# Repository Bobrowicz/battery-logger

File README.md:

# battery-logger
Repository for my digitally controlled dummy load/battery tester

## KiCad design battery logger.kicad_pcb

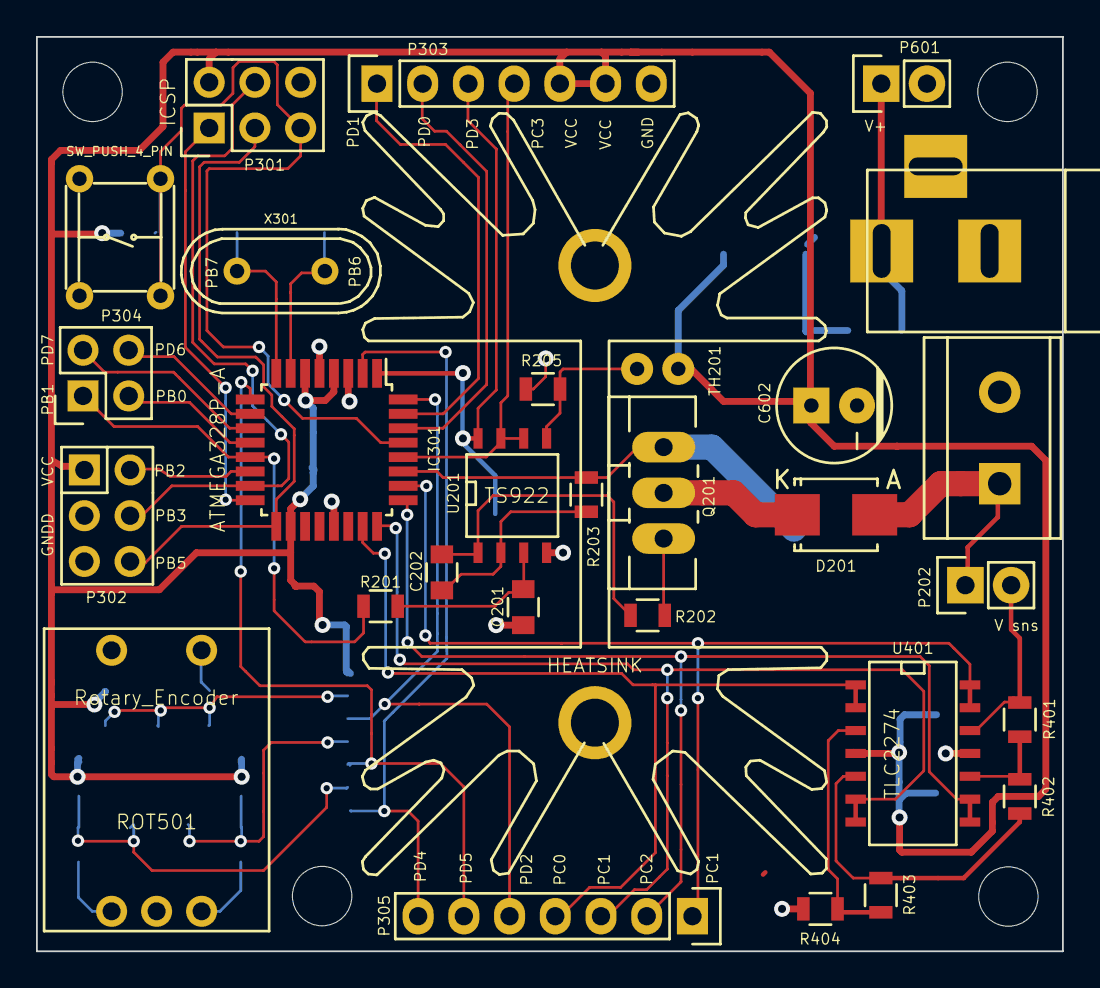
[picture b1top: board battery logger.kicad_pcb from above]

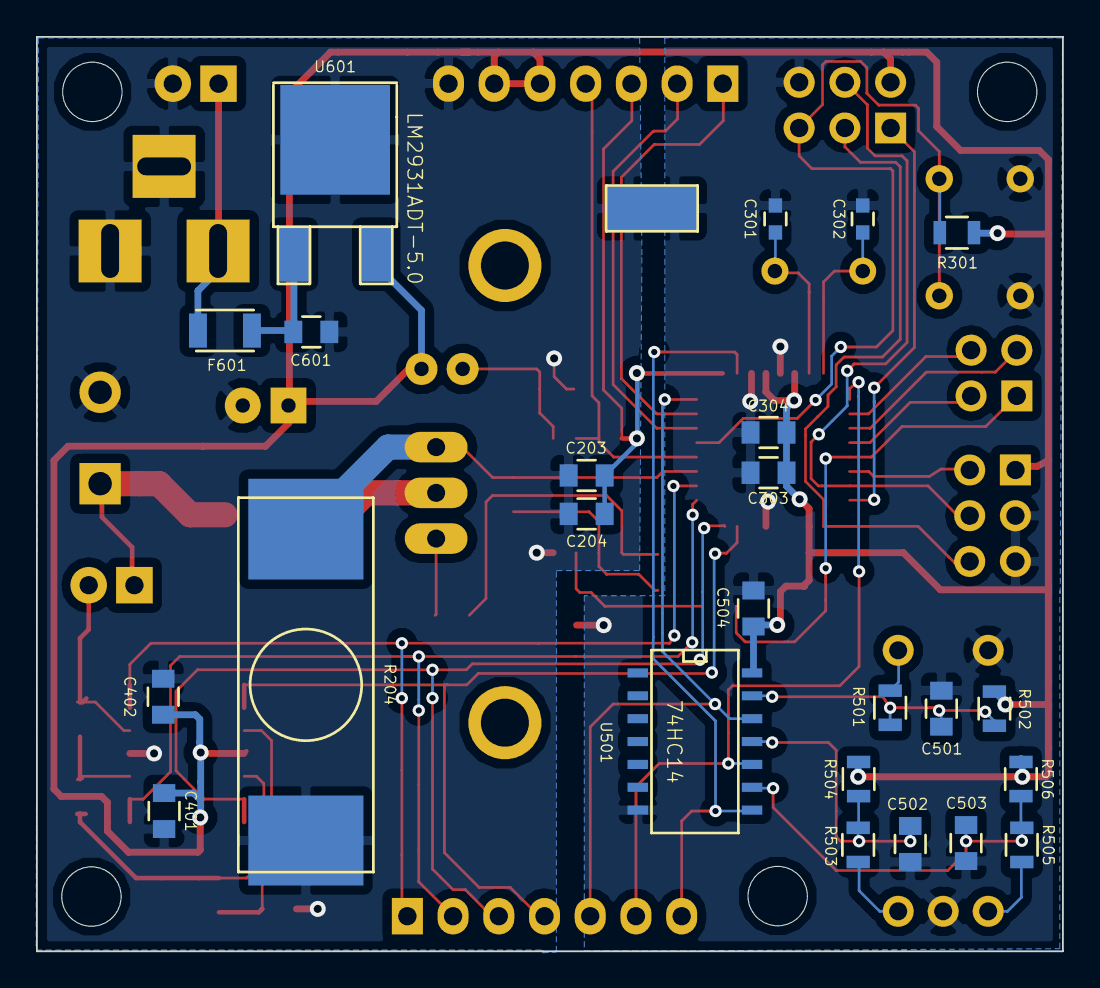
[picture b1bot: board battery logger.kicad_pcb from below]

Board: 2 copper layers, 57.0 x 50.8 mm, 59 parts (25 on the bottom side), 45 nets.

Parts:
C201, C202, C203, C402, C501: 1u; C_0805
C204, C303, C401, C504, C601: 0.1u; C_0805
C301, C302: 18p; C_0603
C304, C502, C503: 0.01u; C_0805
C602: 100u; Capacitor6.4x6RM2.5
CON601: BARREL_JACK
D201: DIODESCH; Diode-SMB_Standard
F601: FUSE; PTC_1206
HS201: HEATSINK; FA-TO220-64E
IC301: ATMEGA328P-A; TQFP-32_7x7mm_Pitch0.8mm
J601: Net_Tie; Net_Tie2
M3 screw hole, M3 screw hole#2, M3 screw hole#3, M3 screw hole#4: VAL**; M3_screw_hole
P201: CONN_01X02; Terminal_Block_1x2_5.08mm
P202, P601: CONN_01X02; Pin_Header_Straight_1x02
P301, P302: CONN_02X03; Pin_Header_Straight_2x03
P303, P305: CONN_01X07; Pin_Header_Straight_1x07
P304: CONN_02X02; Pin_Header_Straight_2x02
Q201: BUK9575; TO-220_FET-GDS_Vertical_LargePads
R201, R203, R205, R301, R401, R502, R504, R506: 10k; R_0805
R202: 100R; R_0805
R204: 1R; 8035_J-Lead
R402, R403, R404, R501, R503, R505: 3.3k; R_0805
ROT501: Rotary_Encoder; PEC11R
SW301: SW_PUSH_4_PIN; B3F-10XX
TH201: THERMISTOR; SolderWirePad_2x_0-8mmDrill
U201: TS922; SOIC-8-N
U401: TLC2274; SOIC-14_N
U501: 74HC14; SOIC-14_N
U601: LM2931ADT-5.0; DPAK-2
X301: CRYSTAL 16MHZ; Crystal_HC49-U_Vertical

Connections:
/Current Sink/AUX: IC301.28, P303.4, U201.6, U201.7
/Current Sink/BATT_V: P202.2, R401.1, U401.12
/Current Sink/ENABLE: C203.1, C204.1, IC301.1, P303.3, U201.8
/Current Sink/I_SNS: IC301.27, Q201.S, R203.1, R204.1
/Current Sink/V_SET: IC301.13, P304.1, R201.1
/Encoder Interface/ENC_A: IC301.2, P305.7, U501.8
/Encoder Interface/ENC_B: IC301.9, P305.6, U501.10
/Encoder Interface/ENC_SW: IC301.32, P305.5, U501.12
/Input Voltage Range Switch/V_SNS1: IC301.26, P305.1, U401.13, U401.14
/Input Voltage Range Switch/V_SNS2: IC301.25, P305.2, U401.8, U401.9
/Input Voltage Range Switch/V_SNS3: IC301.24, P305.3, U401.6, U401.7
/Input Voltage Range Switch/V_SNS4: IC301.23, P305.4, U401.1, U401.2
/Voltage Regulator/Vs: CON601.1, F601.1, P601.1
/uController/CLK: IC301.17, P301.3, P302.6
/uController/DAT: IC301.15, P301.4, P302.4
/uController/LAT: IC301.14, P302.2
/uController/MISO: IC301.16, P301.1
/uController/PB0: IC301.12, P304.3
/uController/PB6: C301.1, IC301.7, X301.1
/uController/PB7: C302.1, IC301.8, X301.2
/uController/PC6: IC301.29, P301.5, R301.2, SW301.1, SW301.4
/uController/PD0: IC301.30, P303.2
/uController/PD1: IC301.31, P303.1
/uController/PD6: IC301.10, P304.4
/uController/PD7: IC301.11, P304.2
GND: C203.2, C204.2, C401.2, C402.2, C601.2, C602.2, CON601.2, CON601.3, J601.1, P201.2, P303.7, P601.2, R204.2, R205.1, R404.2, U201.4, U401.11, U601.2
GNDD: C201.2, C301.2, C302.2, C303.2, C304.2, C501.2, C502.2, C503.2, C504.2, IC301.3, IC301.5, IC301.21, J601.2, P301.6, P302.3, P302.5, ROT501.1, ROT501.4, SW301.2, SW301.3, U501.7
unnamed: C201.1, R201.2, U201.3
unnamed: C202.1, R202.2, U201.1
unnamed: C202.2, R203.2, U201.2
unnamed: C501.1, R501.1, R502.2, U501.13
unnamed: C502.1, R503.1, R504.2, U501.11
unnamed: C503.1, R505.2, R506.2, U501.9
unnamed: C601.1, F601.2, U601.1
unnamed: D201.1, P201.1, P202.1
unnamed: D201.2, Q201.D
unnamed: Q201.G, R202.1
unnamed: R205.2, TH201.2, U201.5
unnamed: R401.2, R402.1, U401.10
unnamed: R402.2, R403.1, U401.5
unnamed: R403.2, R404.1, U401.3
unnamed: R501.2, ROT501.2
unnamed: R503.2, ROT501.5
unnamed: R505.1, ROT501.3
VCC: C303.1, C304.1, C401.1, C402.1, C504.1, C602.1, IC301.4, IC301.6, IC301.18, P301.2, P302.1, P303.5, P303.6, R301.1, R502.1, R504.1, R506.1, TH201.1, U401.4, U501.14, U601.3

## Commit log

2015-02-10 initial schematic with tentative components
2015-02-10 added arduino code
2015-02-10 some code cleanup and comments
2015-02-10 added few parts to schematic
2015-02-12 added LCD connections
2015-02-13 added hierarchical sheets
2015-02-13 more cleanup
2015-02-17 updated schematic
2015-02-22 beginning layout
2015-02-22 initial part placemen
2015-02-24 tweaking part layout
2015-03-02 finished layout
2015-03-02 minor tweaks
2015-03-07 generated gerber files
2015-03-14 BOM update
2015-03-14 firmware rev
2015-03-27 schematic correction
2015-04-04 firmware update
2015-04-05 added some comments to uC source code
2015-04-06 cleaned up some code and added component footprints
2015-04-09 added few comments to code
2015-04-09 minor code change
    tested simplified version of the code for scrolling through menu using
    rotary encoder.
    started working to calibration function
2015-04-10 simplified some menu code
2015-04-11 moved strings to PROGMEM, testing EEPROM code
2015-04-16 got software cal function to mostly work
2015-04-18 some progress on calibration function
2015-04-24 committing in case i mess up what im doing
2015-05-06 added oversampling and decimation to get 12 bits
